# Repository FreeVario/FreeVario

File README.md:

# FreeVario
Freevario is an opensource vario that provides telemetry data to any vario based program such as XCSoar or XCTrack via bluetooth or USB in the form of NMEA sentences. It's a custom build pcb board* featuring:
 <br>
  STM32F405 processor  <br>
  E-Ink display  <br>
  GNSS module <br>
  BMP280 presure sensor <br>
  mpu6050 motion sensor <br>
  HM13 bluetooth module <br>
  SX1276 Lora Modem (for FANET) <br>
  Micro SDcard reader <br>
  Piezo buzzer output <br>
  USB-C connector for OTG and charging <br>  
  SWDIO port
  Signal LED
  CN3055 LiPo charger  
<br>
*The board is development status and there are some errors, don't use it for production or anything

The firmware runs on FreeRtos and STM32 HAL drivers. 

A lot of firmware features still have to be added and developed, but the milestone releases are practically usable

<br>
<br>
<center>

</center>

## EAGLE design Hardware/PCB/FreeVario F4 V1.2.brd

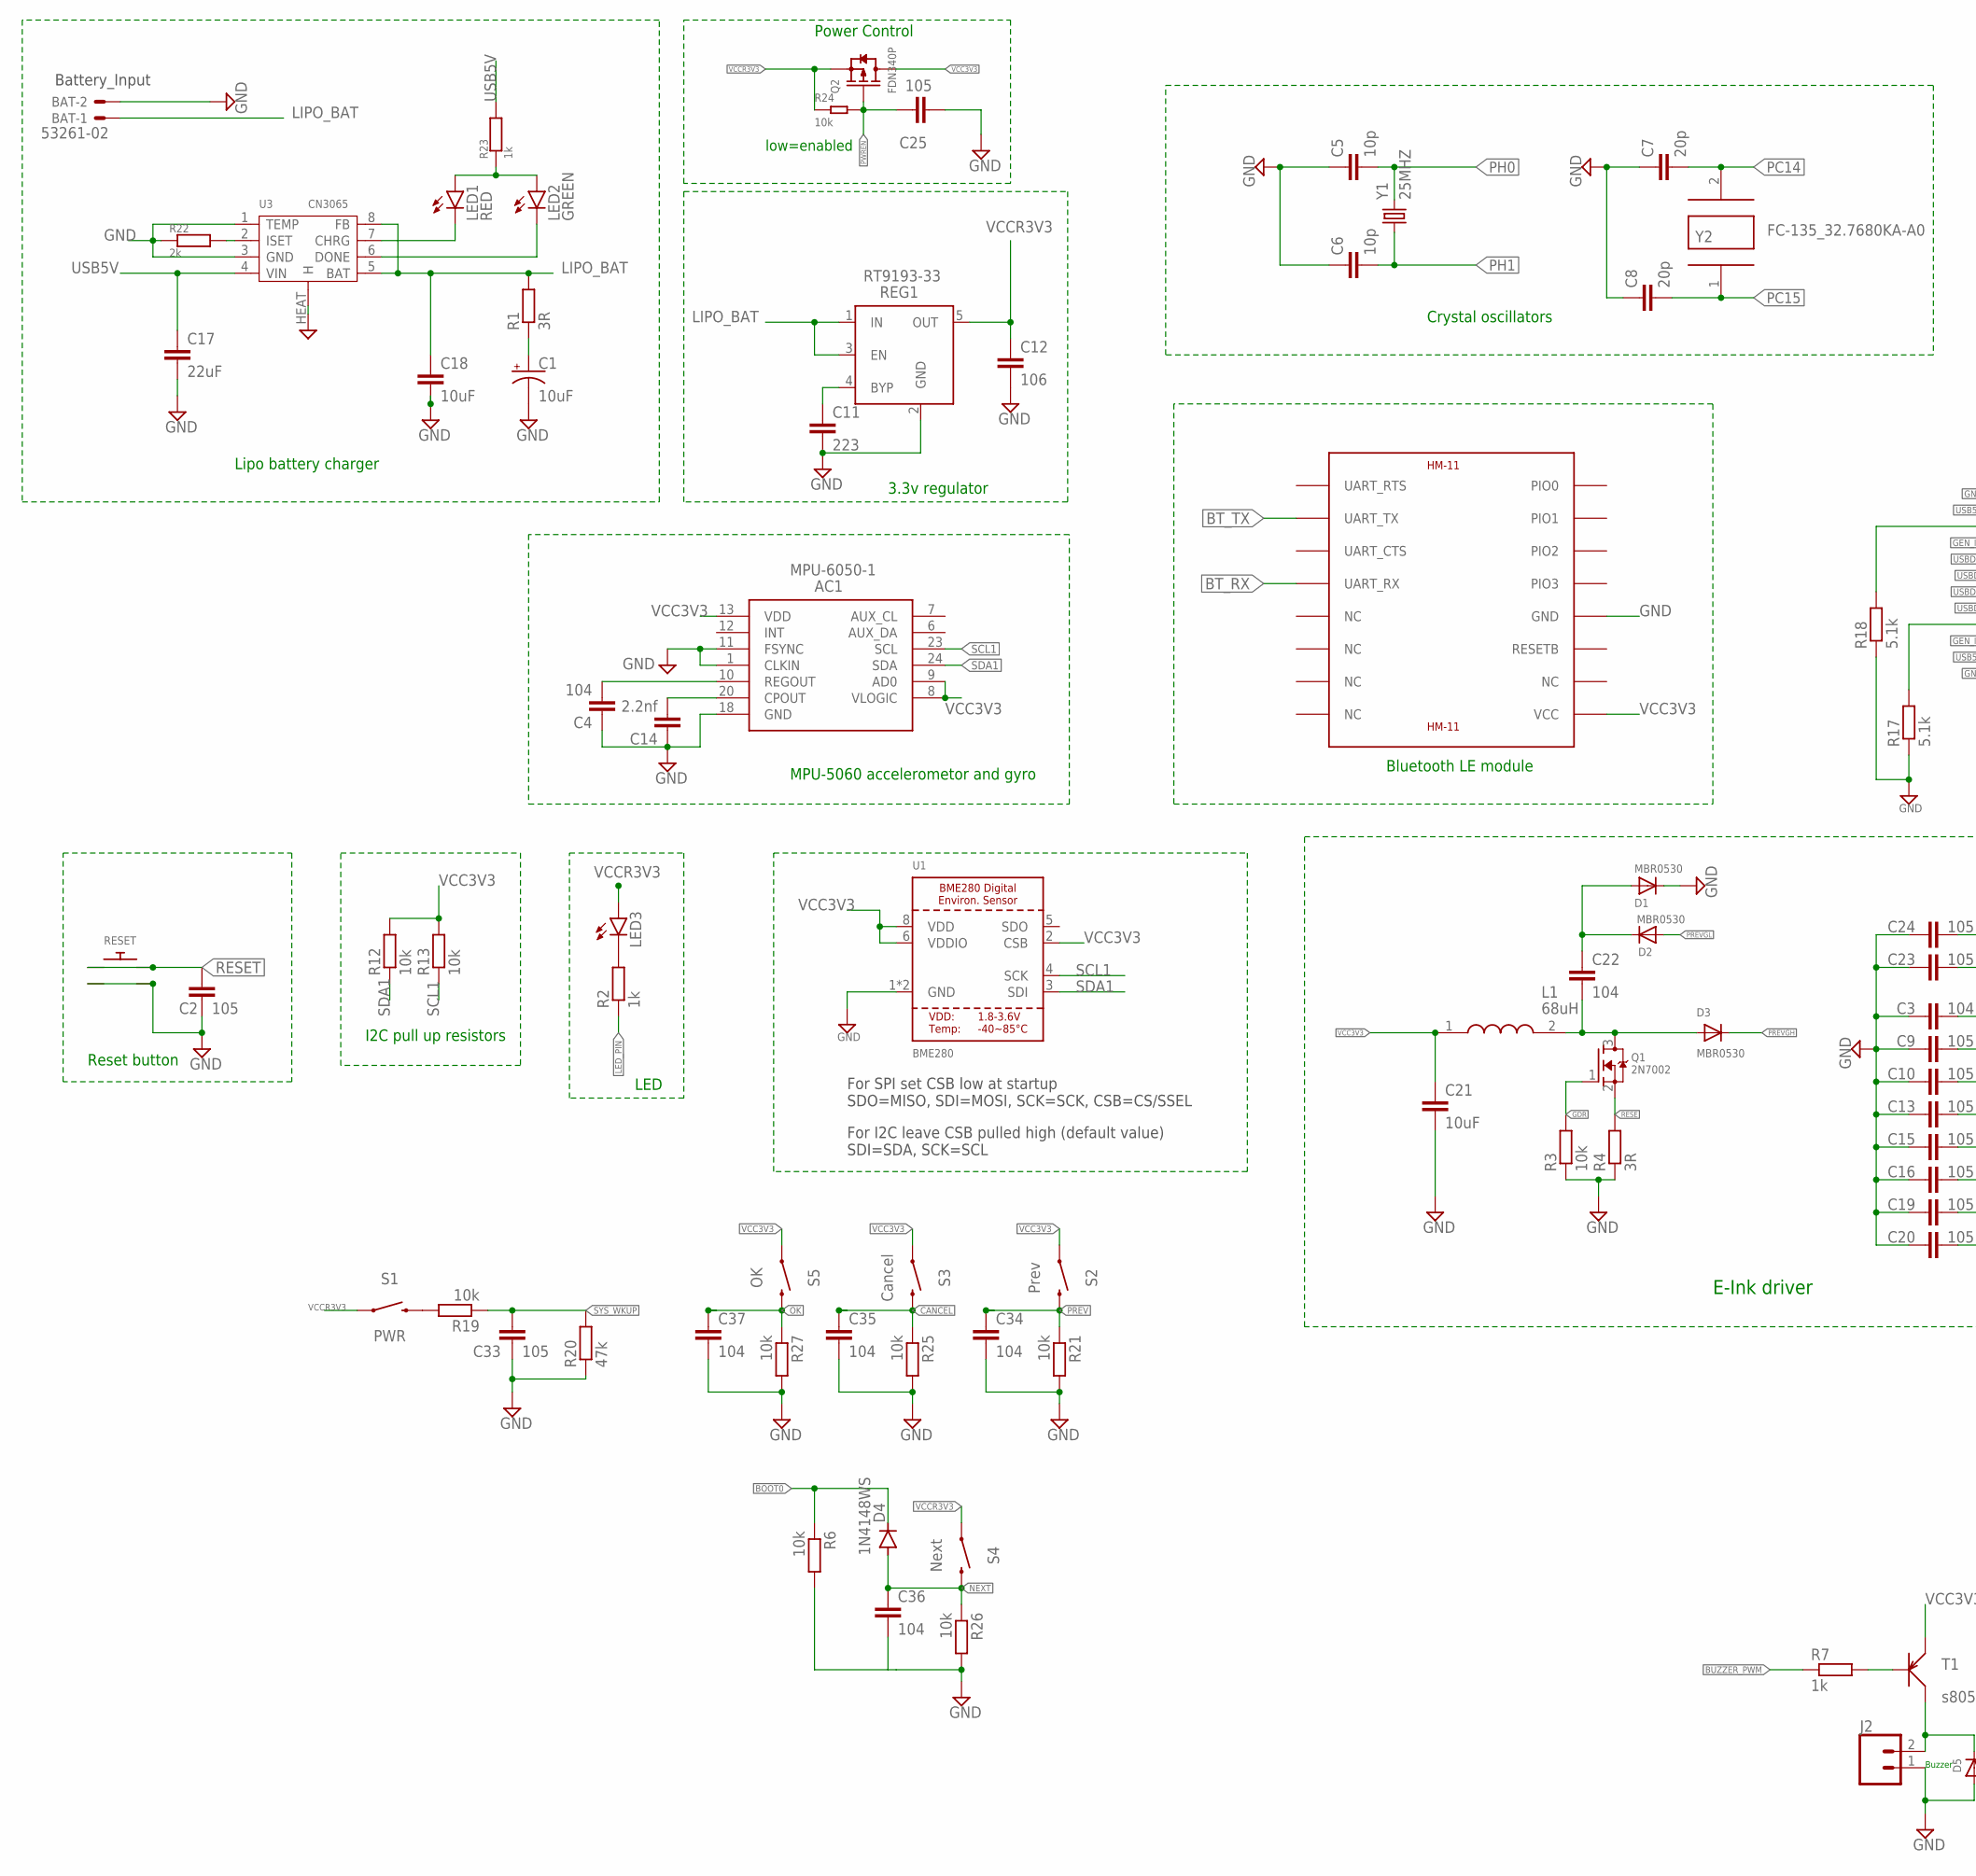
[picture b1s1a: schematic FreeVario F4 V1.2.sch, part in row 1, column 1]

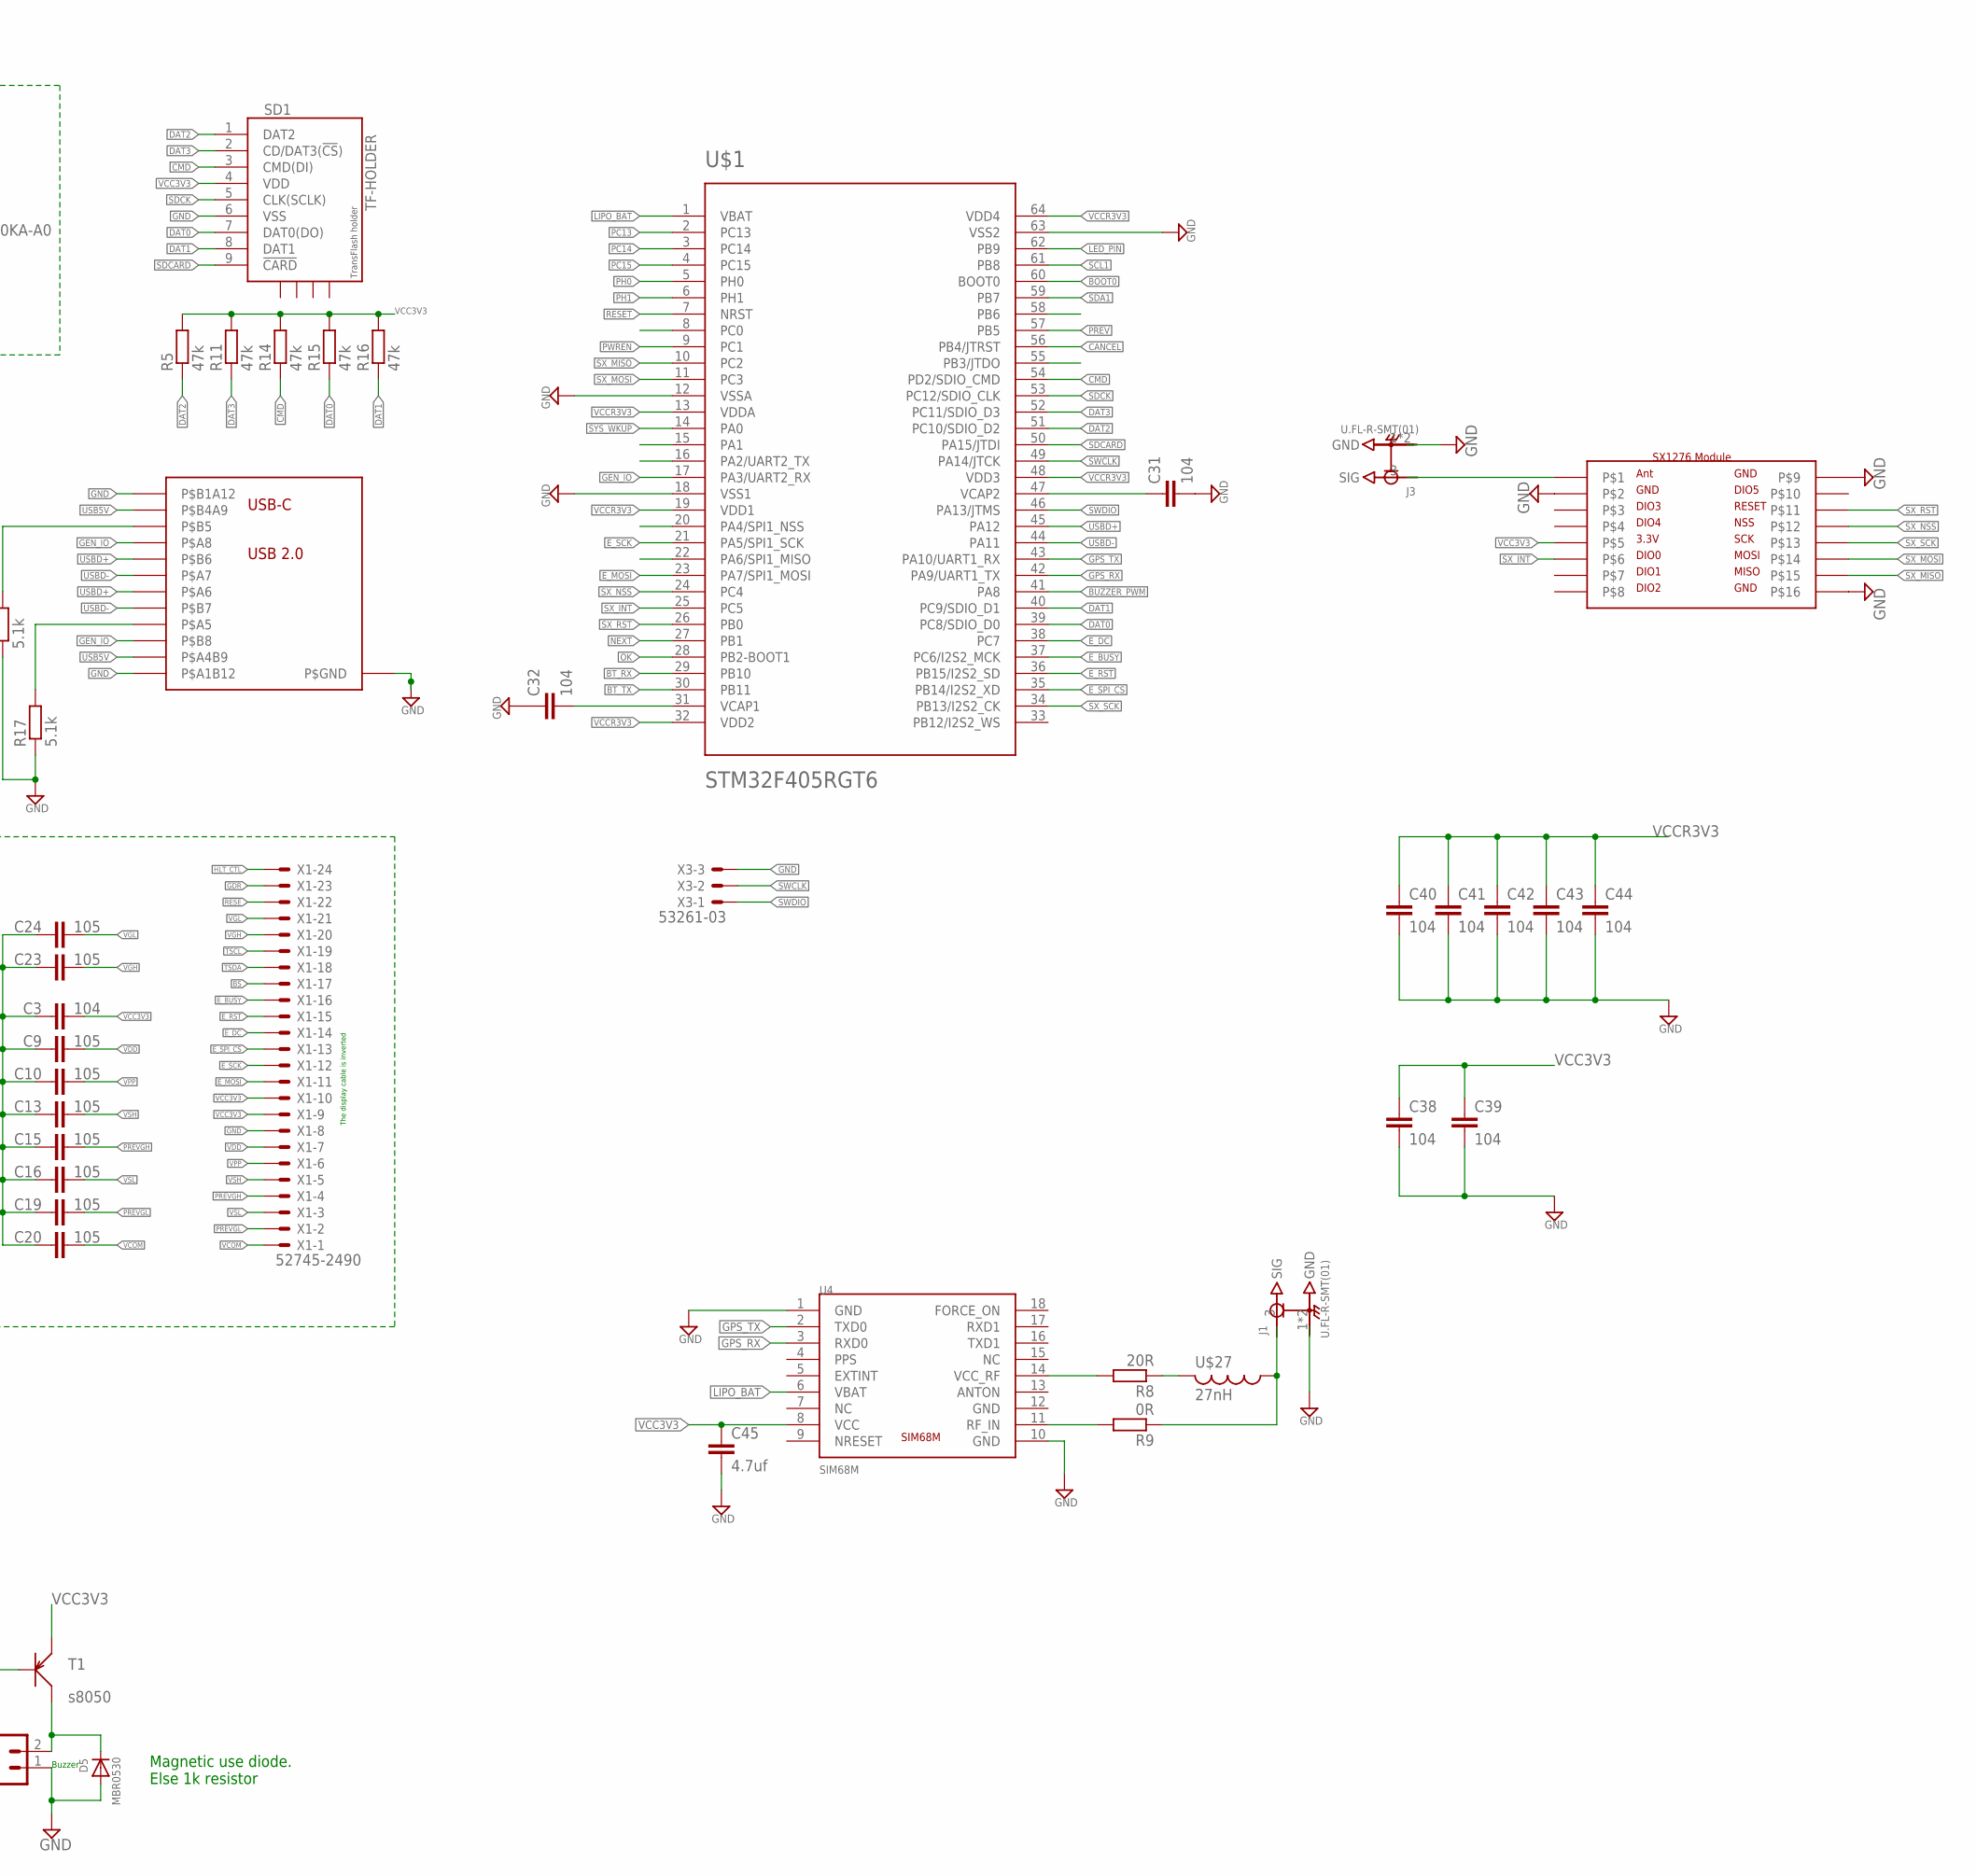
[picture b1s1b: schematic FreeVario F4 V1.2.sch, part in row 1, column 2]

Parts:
AC1: MPU-6050-1; QFN-24-4MM2
BAT: 53261-02
C1: 10uF; EIA3216
C2, C9, C10, C13, C15, C16, C19, C20, C23, C24, C25, C33: 105; C0603K
C3, C4, C22, C31, C32, C34, C35, C36, C37, C38, C39, C40, C41, C42, C43, C44: 104; C0603K
C5, C6: 10p; C0603K
C7, C8: 20p; C0603K
C11: 223; C0603K
C12: 106; C0603K
C14: 2.2nf; C0603K
C17: 22uF; C0805
C18: 10uF; C0805
C21: 10uF; C0603K
C45: 4.7uf; C0603K
D1, D2, D3, D5: MBR0530; SOD-123
D4: 1N4148WS; SOD323-R
HM13: HM-11
J1, J3: U.FL-R-SMT(01); HRS_U.FL-R-SMT(01)
J2: CONN_021X02_NO_SILK; 1X02_NO_SILK
L1: 68uH; INDPM3030X150N
LED1: RED; CHIPLED_0603
LED2: GREEN; CHIPLED_0603
LED3: LEDCHIP-LED0603; CHIP-LED0603
Q1: 2N7002; SOT23
Q2: FDN340P; SOT-23
R1, R4: 3R; R0603
R2, R7, R23: 1k; R0603
R3, R6, R12, R13, R19, R21, R24, R25, R26, R27: 10k; R0603
R5, R11, R14, R15, R16, R20: 47k; R0603
R8: 20R; R0603
R9: 0R; R0603
R17, R18: 5.1k; R0603
R22: 2k; R0603
REG1: RT9193-33; SOT23-5
RESET: TS-015A
S1: PWR; TACTILE_SWITCH_SMD_6.0X3.5MM
S2: Prev; TACTILE_SWITCH_SMD_6.0X3.5MM
S3: Cancel; TACTILE_SWITCH_SMD_6.0X3.5MM
S4: Next; TACTILE_SWITCH_SMD_6.0X3.5MM
S5: OK; TACTILE_SWITCH_SMD_6.0X3.5MM
SD1: TF-HOLDER; TF-PULL
T1: s8050; SOT-23
U1: BME280
U3: CN3065; DFN-8
U4: SIM68M
U$1: STM32F405RGT6; TQFP64
U$2: USB-C_LOWSPEED
U$4: MODULESX1276
U$27: 27nH; RESC0603_M
X1: 52745-2490
X3: 53261-03
Y1: 25MHZ; 5.0X3.2_2
Y2: FC-135_32.7680KA-A0; XTAL_FC-135_32.7680KA-A0

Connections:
BOOT0: D4.C, R6.1, U$1.60 (BOOT0)
BS: X1.17
BT_RX: HM13.UART_RX, U$1.29 (PB10)
BT_TX: HM13.UART_TX, U$1.30 (PB11)
BUZZER_PWM: R7.1, U$1.41 (PA8)
CANCEL: C35.1, R25.1, S3.2, U$1.56 (PB4/JTRST)
CMD: R14.1, SD1.3 (CMD(DI)), U$1.54 (PD2/SDIO_CMD)
DAT0: R15.1, SD1.7 (DAT0(DO)), U$1.39 (PC8/SDIO_D0)
DAT1: R16.1, SD1.8 (DAT1), U$1.40 (PC9/SDIO_D1)
DAT2: R5.1, SD1.1 (DAT2), U$1.51 (PC10/SDIO_D2)
DAT3: R11.1, SD1.2 (CD/DAT3(!CS!)), U$1.52 (PC11/SDIO_D3)
E_BUSY: U$1.37 (PC6/I2S2_MCK), X1.16
E_DC: U$1.38 (PC7), X1.14
E_MOSI: U$1.23 (PA7/SPI1_MOSI), X1.11
E_RST: U$1.36 (PB15/I2S2_SD), X1.15
E_SCK: U$1.21 (PA5/SPI1_SCK), X1.12
E_SPI_CS: U$1.35 (PB14/I2S2_XD), X1.13
GDR: Q1.1 (G), R3.2, X1.23
GEN_IO: U$1.17 (PA3/UART2_RX), U$2.P$A8, U$2.P$B8
GND: AC1.1 (CLKIN), AC1.11 (FSYNC), AC1.18 (GND), BAT.2, C1.-, C2.2, C3.1, C4.1, C5.1, C6.1, C7.1, C8.1, C9.1, C10.1, C11.2, C12.2, C13.1, C14.1, C15.1, C16.1, C17.2, C18.2, C19.1, C20.1, C21.2, C23.1, C24.1, C25.2, C31.2, C32.1, C33.2, C34.2, C35.2, C36.2, C37.2, C38.2, C39.2, C40.2, C41.2, C42.2, C43.2, C44.2, C45.2, D1.C, D5.A, HM13.GND, J1.1 (GND), J1.2 (GND), J2.1, J3.1 (GND), J3.2 (GND), R3.1, R4.1, R6.2, R17.1, R18.1, R20.1, R21.2, R22.1, R25.2, R26.2, R27.2, REG1.2 (GND), RESET.P$2, RESET.P$4, SD1.6 (VSS), U1.1 (GND), U1.7 (GND), U3.1 (TEMP), U3.3 (GND), U3.HEAT (H), U4.1 (GND), U4.10 (GND), U4.12 (GND), U$1.12 (VSSA), U$1.18 (VSS1), U$1.63 (VSS2), U$2.P$1 (P$GND), U$2.P$2 (P$GND), U$2.P$20 (P$GND), U$2.P$21 (P$GND), U$2.P$22 (P$GND), U$2.P$23 (P$GND), U$2.P$A1B12, U$2.P$B1A12, U$4.SX2, U$4.SX9, U$4.SX16, X1.8, X3.3
GPS_RX: U4.3 (RXD0), U$1.42 (PA9/UART1_TX)
GPS_TX: U4.2 (TXD0), U$1.43 (PA10/UART1_RX)
HLT_CTL: X1.24
LED_PIN: R2.1, U$1.62 (PB9)
LIPO_BAT: BAT.1, C18.1, R1.2, REG1.1 (IN), REG1.3 (EN), U3.5 (BAT), U3.8 (FB), U4.6 (VBAT), U$1.1 (VBAT)
unnamed: LED1.A, LED2.A, R23.1
unnamed: LED1.C, U3.7 (CHRG)
unnamed: LED2.C, U3.6 (DONE)
unnamed: C1.+, R1.1
unnamed: C11.1, REG1.4 (BYP)
unnamed: J1.3 (SIG), R9.1, U$27.1
unnamed: LED3.C, R2.2
unnamed: C22.2, D3.A, L1.2, Q1.3 (D)
unnamed: R19.2, S1.2
unnamed: R8.1, U$27.2
unnamed: C22.1, D1.A, D2.C
unnamed: J3.3 (SIG), U$4.SX1
unnamed: D5.C, J2.2, T1.3 (C)
unnamed: R7.2, T1.1 (B)
unnamed: AC1.10 (REGOUT), C4.2
unnamed: R8.2, U4.14 (VCC_RF)
unnamed: R22.2, U3.2 (ISET)
unnamed: AC1.20 (CPOUT), C14.2
unnamed: R9.2, U4.11 (RF_IN)
unnamed: C32.2, U$1.31 (VCAP1)
unnamed: C31.1, U$1.47 (VCAP2)
unnamed: R17.2, U$2.P$A5
unnamed: R18.2, U$2.P$B5
NEXT: C36.1, D4.A, R26.1, S4.2, U$1.27 (PB1)
OK: C37.1, R27.1, S5.2, U$1.28 (PB2-BOOT1)
PC0: U$1.8 (PC0)
PC13: U$1.2 (PC13)
PC14: C7.2, U$1.3 (PC14), Y2.2
PC15: C8.2, U$1.4 (PC15), Y2.1
PH0: C5.2, U$1.5 (PH0), Y1.2
PH1: C6.2, U$1.6 (PH1), Y1.1
PREV: C34.1, R21.1, S2.2, U$1.57 (PB5)
PREVGH: C15.2, D3.C, X1.4
PREVGL: C19.2, D2.A, X1.2
PWREN: C25.1, Q2.1 (G), R24.2, U$1.9 (PC1)
RESE: Q1.2 (S), R4.2, X1.22
RESET: C2.1, RESET.P$1, RESET.P$3, U$1.7 (NRST)
SCL1: AC1.23 (SCL), R13.1, U1.4 (SCK), U$1.61 (PB8)
SDA1: AC1.24 (SDA), R12.1, U1.3 (SDI), U$1.59 (PB7)
SDCARD: SD1.9 (!CARD), U$1.50 (PA15/JTDI)
SDCK: SD1.5 (CLK(SCLK)), U$1.53 (PC12/SDIO_CLK)
SWCLK: U$1.49 (PA14/JTCK), X3.2
SWDIO: U$1.46 (PA13/JTMS), X3.1
SX_INT: U$1.25 (PC5), U$4.SX6
SX_MISO: U$1.10 (PC2), U$4.SX15
SX_MOSI: U$1.11 (PC3), U$4.SX14
SX_NSS: U$1.24 (PC4), U$4.SX12
SX_RST: U$1.26 (PB0), U$4.SX11
SX_SCK: U$1.34 (PB13/I2S2_CK), U$4.SX13
SYS_WKUP: C33.1, R19.1, R20.2, U$1.14 (PA0)
TSCL: X1.19
TSDA: X1.18
USB5V: C17.1, R23.2, U3.4 (VIN), U$2.P$A4B9, U$2.P$B4A9
USBD+: U$1.45 (PA12), U$2.P$A6, U$2.P$B6
USBD-: U$1.44 (PA11), U$2.P$A7, U$2.P$B7
VCC3V3: AC1.8 (VLOGIC), AC1.9 (AD0), AC1.13 (VDD), C3.2, C21.1, C38.1, C39.1, C45.1, HM13.VCC, L1.1, Q2.3 (D), R5.2, R11.2, R12.2, R13.2, R14.2, R15.2, R16.2, S2.1, S3.1, S5.1, SD1.4 (VDD), T1.2 (E), U1.2 (CSB), U1.6 (VDDIO), U1.8 (VDD), U4.8 (VCC), U$4.SX5, X1.9, X1.10
VCCR3V3: C12.1, C40.1, C41.1, C42.1, C43.1, C44.1, LED3.A, Q2.2 (S), R24.1, REG1.5 (OUT), S1.1, S4.1, U$1.13 (VDDA), U$1.19 (VDD1), U$1.32 (VDD2), U$1.48 (VDD3), U$1.64 (VDD4)
VCOM: C20.2, X1.1
VDD: C9.2, X1.7
VGH: C23.2, X1.20
VGL: C24.2, X1.21
VPP: C10.2, X1.6
VSH: C13.2, X1.5
VSL: C16.2, X1.3

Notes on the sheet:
Battery_Input
Lipo battery charger
Bluetooth LE module
MPU-5060 accelerometor and gyro
3.3v regulator
Reset button
I2C pull up resistors
LED
For SPI set CSB low at startup SDO=MISO, SDI=MOSI, SCK=SCK, CSB=CS/SSEL
For I2C leave CSB pulled high (default value) SDI=SDA, SCK=SCL
Crystal oscillators
The display cable is inverted
Power Control
low=enabled
E-Ink driver
Buzzer
Magnetic use diode. Else 1k resistor

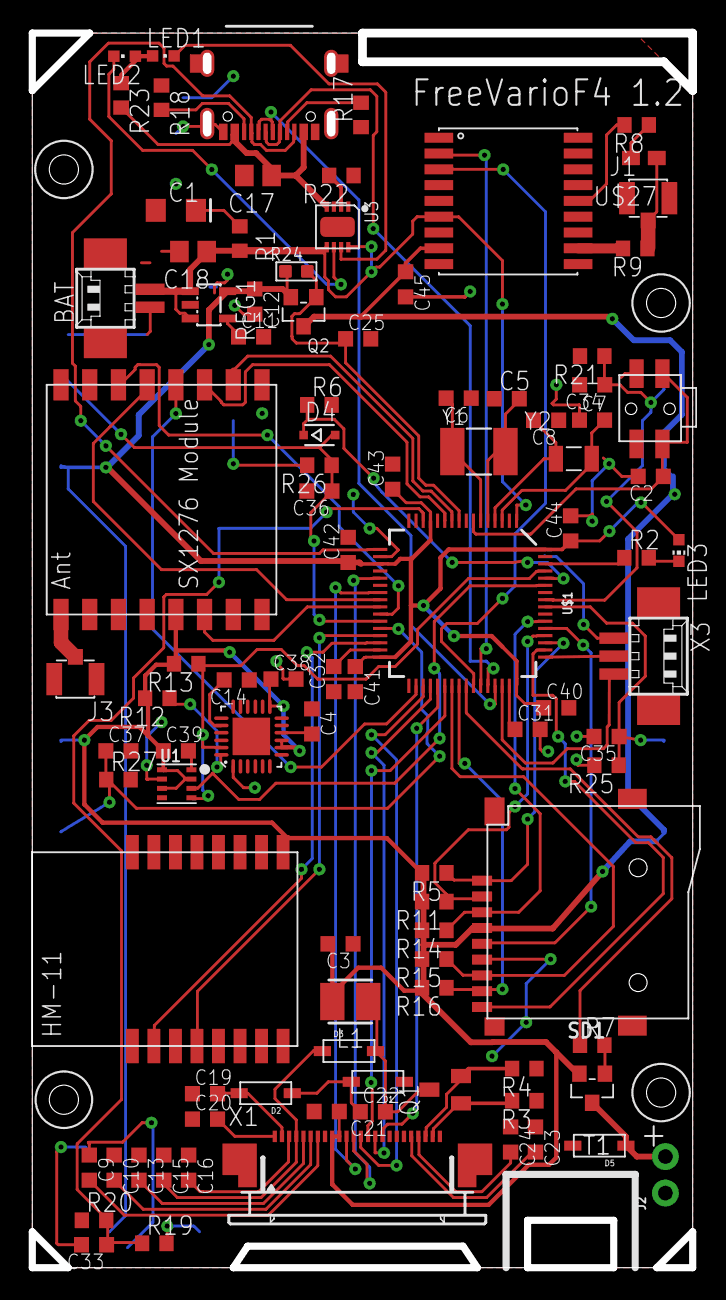
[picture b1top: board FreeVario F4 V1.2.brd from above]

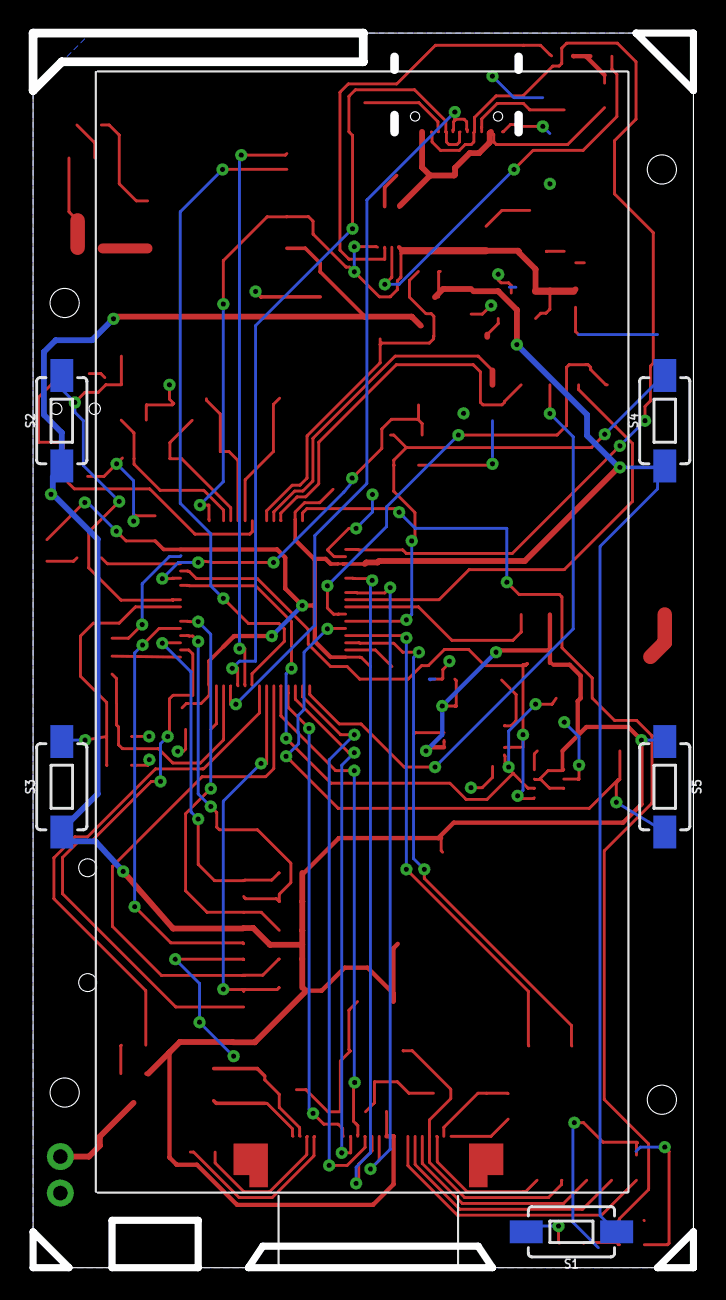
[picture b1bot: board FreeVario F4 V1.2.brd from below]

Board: 2 copper layers, 46.0 x 86.0 mm, 103 parts (5 on the bottom side), 83 nets.

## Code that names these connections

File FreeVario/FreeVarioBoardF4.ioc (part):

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Mcu.Name=STM32F405RGTx
Mcu.Package=LQFP64
Mcu.UserName=STM32F405RGTx
PA0-WKUP.GPIOParameters=GPIO_Label
PA0-WKUP.GPIO_Label=PWRBUTTON
PA0-WKUP.Mode=SYS_WakeUp0
PA0-WKUP.Signal=SYS_WKUP
PA10.GPIOParameters=GPIO_Label
PA10.GPIO_Label=GPS_USART_RX
PA10.Mode=Asynchronous
PA10.Signal=USART1_RX
PA11.Mode=Device_Only
PA11.Signal=USB_OTG_FS_DM
PA12.Mode=Device_Only
PA12.Signal=USB_OTG_FS_DP
PA13.Mode=Serial_Wire
PA13.Signal=SYS_JTMS-SWDIO
PA14.Mode=Serial_Wire
PA14.Signal=SYS_JTCK-SWCLK
PA15.GPIOParameters=GPIO_Label
PA15.GPIO_Label=SDCARD
PA15.Signal=GPIO_Input
PA5.Mode=Simplex_Bidirectional_Master
PA5.Signal=SPI1_SCK
PA7.Mode=Simplex_Bidirectional_Master
PA7.Signal=SPI1_MOSI
PA8.GPIOParameters=GPIO_PuPd,GPIO_Label
PA8.GPIO_Label=BUZZER_PWM
PA8.GPIO_PuPd=GPIO_NOPULL
PA8.Signal=S_TIM1_CH1
PA9.GPIOParameters=GPIO_Label
PA9.GPIO_Label=GPS_USART_TX
PA9.Mode=Asynchronous
PA9.Signal=USART1_TX
PB0.GPIOParameters=GPIO_Label
PB0.GPIO_Label=SX_RST
PB0.Signal=GPIO_Output
PB1.GPIOParameters=GPIO_Label
PB1.GPIO_Label=BTN_PREV
PB1.Signal=GPXTI1
PB10.GPIOParameters=GPIO_Label
PB10.GPIO_Label=BT_USART_TX
PB10.Mode=Asynchronous
PB10.Signal=USART3_TX
PB11.GPIOParameters=GPIO_Label
PB11.GPIO_Label=BT_USART_RX
PB11.Mode=Asynchronous
PB11.Signal=USART3_RX
PB13.Mode=Full_Duplex_Master
PB13.Signal=SPI2_SCK
PB14.GPIOParameters=GPIO_Label
PB14.GPIO_Label=SPI_CS
PB14.Signal=GPIO_Output
PB15.GPIOParameters=GPIO_Label
PB15.GPIO_Label=RST
PB15.Signal=GPIO_Output
PB2.GPIOParameters=GPIO_Label
PB2.GPIO_Label=BTN_OK
PB2.Signal=GPXTI2
PB4.GPIOParameters=GPIO_Label
PB4.GPIO_Label=BTN_CANCEL
PB4.Signal=GPXTI4
PB5.GPIOParameters=GPIO_Label
PB5.GPIO_Label=BTN_NEXT
PB5.Signal=GPXTI5
PB7.Mode=I2C
PB7.Signal=I2C1_SDA
PB8.Mode=I2C
PB8.Signal=I2C1_SCL
PB9.GPIOParameters=GPIO_Label
PB9.GPIO_Label=LED
PB9.Signal=GPIO_Output
PC10.GPIOParameters=GPIO_PuPd
PC10.GPIO_PuPd=GPIO_PULLUP
PC10.Mode=SD_4_bits_Wide_bus
PC10.Signal=SDIO_D2
PC11.GPIOParameters=GPIO_PuPd
PC11.GPIO_PuPd=GPIO_PULLUP
PC11.Mode=SD_4_bits_Wide_bus
PC11.Signal=SDIO_D3
PC12.Mode=SD_4_bits_Wide_bus
PC12.Signal=SDIO_CK
PC14-OSC32_IN.Mode=LSE-External-Oscillator
PC14-OSC32_IN.Signal=RCC_OSC32_IN
PC15-OSC32_OUT.Mode=LSE-External-Oscillator
PC15-OSC32_OUT.Signal=RCC_OSC32_OUT
PC2.Mode=Full_Duplex_Master
PC2.Signal=SPI2_MISO
PC3.Mode=Full_Duplex_Master
PC3.Signal=SPI2_MOSI
PC4.GPIOParameters=GPIO_Label
PC4.GPIO_Label=SX_NSS
PC4.Signal=GPIO_Output
PC5.GPIOParameters=GPIO_Label
PC5.GPIO_Label=SX_INT
PC5.Signal=GPIO_Output
PC6.GPIOParameters=GPIO_Label
PC6.GPIO_Label=BUSY
PC6.Signal=GPIO_Input
PC7.GPIOParameters=GPIO_Label
PC7.GPIO_Label=DC
PC7.Signal=GPIO_Output
PC8.GPIOParameters=GPIO_PuPd
PC8.GPIO_PuPd=GPIO_PULLUP
PC8.Mode=SD_4_bits_Wide_bus
PC8.Signal=SDIO_D0
PC9.GPIOParameters=GPIO_PuPd
PC9.GPIO_PuPd=GPIO_PULLUP
PC9.Mode=SD_4_bits_Wide_bus
PC9.Signal=SDIO_D1
PD2.GPIOParameters=GPIO_PuPd
PD2.GPIO_PuPd=GPIO_PULLUP
PD2.Mode=SD_4_bits_Wide_bus
PD2.Signal=SDIO_CMD
PH0-OSC_IN.Mode=HSE-External-Oscillator
PH0-OSC_IN.Signal=RCC_OSC_IN
PH1-OSC_OUT.Mode=HSE-External-Oscillator
PH1-OSC_OUT.Signal=RCC_OSC_OUT
RCC.HSE_VALUE=8000000
RCC.SYSCLKFreq_VALUE=120000000
RCC.SYSCLKSource=RCC_SYSCLKSOURCE_PLLCLK
board=custom

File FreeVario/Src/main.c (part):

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  __HAL_RCC_GPIOD_CLK_ENABLE();

  /*Configure GPIO pin Output Level */
  HAL_GPIO_WritePin(GPIOC, PWR_EN_Pin|SX_NSS_Pin|DC_Pin, GPIO_PIN_RESET);

  /*Configure GPIO pin Output Level */
  HAL_GPIO_WritePin(SX_RST_GPIO_Port, SX_RST_Pin, GPIO_PIN_SET);

  /*Configure GPIO pin Output Level */
  HAL_GPIO_WritePin(GPIOB, SPI_CS_Pin|RST_Pin|LED_Pin, GPIO_PIN_RESET);

  /*Configure GPIO pins : PC13 PC0 */
  GPIO_InitStruct.Pin = GPIO_PIN_13|GPIO_PIN_0;
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  GPIO_InitStruct.Pull = GPIO_NOPULL;
  HAL_GPIO_Init(PWRBUTTON_GPIO_Port, &GPIO_InitStruct);

  /*Configure GPIO pins : PA1 PA2 PA3 PA4 
                           PA6 */
  GPIO_InitStruct.Pin = GPIO_PIN_1|GPIO_PIN_2|GPIO_PIN_3|GPIO_PIN_4 
                          |GPIO_PIN_6;
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  GPIO_InitStruct.Pull = GPIO_NOPULL;
  HAL_GPIO_Init(GPIOA, &GPIO_InitStruct);

  /*Configure GPIO pins : SX_NSS_Pin DC_Pin */
  GPIO_InitStruct.Pin = SX_NSS_Pin|DC_Pin;
  GPIO_InitStruct.Mode = GPIO_MODE_OUTPUT_PP;
  GPIO_InitStruct.Pull = GPIO_NOPULL;
  GPIO_InitStruct.Speed = GPIO_SPEED_FREQ_LOW;
  HAL_GPIO_Init(GPIOC, &GPIO_InitStruct);

  /*Configure GPIO pins : SX_INT_Pin BUSY_Pin */
  GPIO_InitStruct.Pin = SX_INT_Pin|BUSY_Pin;
  GPIO_InitStruct.Mode = GPIO_MODE_INPUT;
  GPIO_InitStruct.Pull = GPIO_NOPULL;
  HAL_GPIO_Init(GPIOC, &GPIO_InitStruct);

  /*Configure GPIO pins : SX_RST_Pin SPI_CS_Pin RST_Pin LED_Pin */
  GPIO_InitStruct.Pin = SX_RST_Pin|SPI_CS_Pin|RST_Pin|LED_Pin;
  GPIO_InitStruct.Mode = GPIO_MODE_OUTPUT_PP;
  GPIO_InitStruct.Pull = GPIO_NOPULL;
  GPIO_InitStruct.Speed = GPIO_SPEED_FREQ_LOW;
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  GPIO_InitStruct.Pull = GPIO_NOPULL;
  HAL_GPIO_Init(GPIOB, &GPIO_InitStruct);

  /*Configure GPIO pin : SDCARD_Pin */
  GPIO_InitStruct.Pin = SDCARD_Pin;
  GPIO_InitStruct.Mode = GPIO_MODE_INPUT;
  GPIO_InitStruct.Pull = GPIO_NOPULL;
  HAL_GPIO_Init(SDCARD_GPIO_Port, &GPIO_InitStruct);

  /* EXTI interrupt init*/
  HAL_NVIC_SetPriority(EXTI0_IRQn, 5, 0);
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
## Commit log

2019-02-09 Initial
2019-02-09 Config changes
2019-02-09 Changed resulting files to FreeVario
2019-02-09 Added takeoff and landing timestamps from RTC
2019-02-09 Changed copyright notice to FreeVario
2019-02-12 Added periodic summary log file updates
2019-02-13 Started with dynamic display drawing
2019-02-14 Added comment
2019-02-14 Added box info
2019-02-14 Added display units
2019-03-07 Changes to adapt the new board
2019-03-08 Accl working
2019-03-16 Testing Lora net
2019-03-16 Added macros to control RTOS tasks
2019-04-03 Bug fixes
2019-04-04 Added button control display refresh and some bug fixes
2019-04-04 Changed flight status global sections
2019-04-04 Switch from RTC to GPS timer. STM32 RTC HAL is not very functional.
2019-04-05 Added new fonts. Changed display
2019-04-05 Replaced and added new fonts.
2019-04-05 Increased GPS buffer, added GPS icon
2019-04-05 Set theme jekyll-theme-cayman
2019-04-05 Create CNAME
2019-04-06 Added WWDG to the audio task
2019-04-06 Reduced sartup delay
2019-04-07 Added mute function, fixed BT race condition
2019-04-07 Fixed NMEA sentences.
2019-04-07 Added flight plan checklist to the powedown screen
2019-04-07 Changed audio frequency to better match piezo resonance.
2019-04-08 Changed pressure sensor sample rate to 100ms
2019-04-08 Changed vario calculations from 10 x 100ms to 10 x 50ms x 2.
2019-04-09 Fixed mute function, added GNSS calibration to baro altitude
2019-04-10 Added restart staus flag in the backup registers
2019-04-10 Removed LED flashing
2019-04-11 Changed filname. Corrected NMEA bat level
2019-04-11 Started testing with a kalman filter.
2019-04-12 Added more adaptions to the filter
2019-04-14 Added adaptive vario and optional kelman filter for testing
2019-04-14 Reactivated power delay switch
2019-04-15 Replaced sqrt with sqrtf. Improved audio
2019-04-15 Code format and cleanup
2019-04-15 Changed task to delay until.
2019-04-15 Corrected battery voltage reading
2019-04-16 Updated GPS lib. Switched double to float for the FPU usage
2019-04-16 Auto enable USB on release mode
2019-04-18 Lower sample rate for humidity
2019-04-18 Testing the PWM options
2019-04-29 Removed globaldata.h
2019-05-12 Added support for 1.2 board verions
2019-05-15 Tested Lora radio
2019-05-19 Added vbat to log
2019-05-20 Changed adaptive vario to use sensor struct. Added extra sdcard mount
2019-05-20 Fixed startup wild values
2019-05-20 Lowerd the e-ink spi speed to 7.5 MB/s
2019-05-26 Sync logging with gps
2019-05-28 Added GPX logging
2019-05-30 Completed gpx track format
2019-05-30 Added alternative status display
2019-05-31 Better SDcard loaded detection
2019-05-31 Started display from bmp file
2019-06-02 Added extra mutex control
2019-06-02 Added extra check for gpx
2019-06-03 Added file close to shutdown
2019-06-03 Increased stack sizes
2019-06-04 Increased heap size, added SD keepalive file
2019-06-11 Fixed NMEA CRC
2019-06-12 Added gps speed lock
2019-09-14 Added Case and Pcb design
2019-09-14 Not needed

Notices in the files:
FreeVario/Src/main.c:
(C) COPYRIGHT STMicroelectronics *****END OF FILE
parts and their libraries:
crystal-geyer_V1_0: Copyright: Geyer-Electronic
SparkFun-IC-Microcontroller: Licensing: Creative Commons ShareAlike 4.0 International - https://creativecommons.org/licenses/by-sa/4.0
